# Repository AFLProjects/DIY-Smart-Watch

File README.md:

Project Overview
========

The project is an MCU based smartwatch. The MCU which is used is the [ATMEGA32U4](http://ww1.microchip.com/downloads/en/devicedoc/atmel-7766-8-bit-avr-atmega16u4-32u4_datasheet.pdf). The whole project is powered with the [3.7V 380mAh LQ-S1](https://i.ibb.co/z8Tqzwt/Capture.png) lithium battery.
I am also using an TFT 240 x 240 IPS [ST7789](https://www.rhydolabz.com/documents/33/ST7789.pdf) display with [SPI](https://fr.wikipedia.org/wiki/Serial_Peripheral_Interface). And the [RV-3028-C7](https://www.mouser.fr/datasheet/2/530/RV-3028-C7-1524919.pdf) Extreme Low Power RTC Module with [I2C](https://fr.wikipedia.org/wiki/I2C). In future revisions, an accelerometer will be added.

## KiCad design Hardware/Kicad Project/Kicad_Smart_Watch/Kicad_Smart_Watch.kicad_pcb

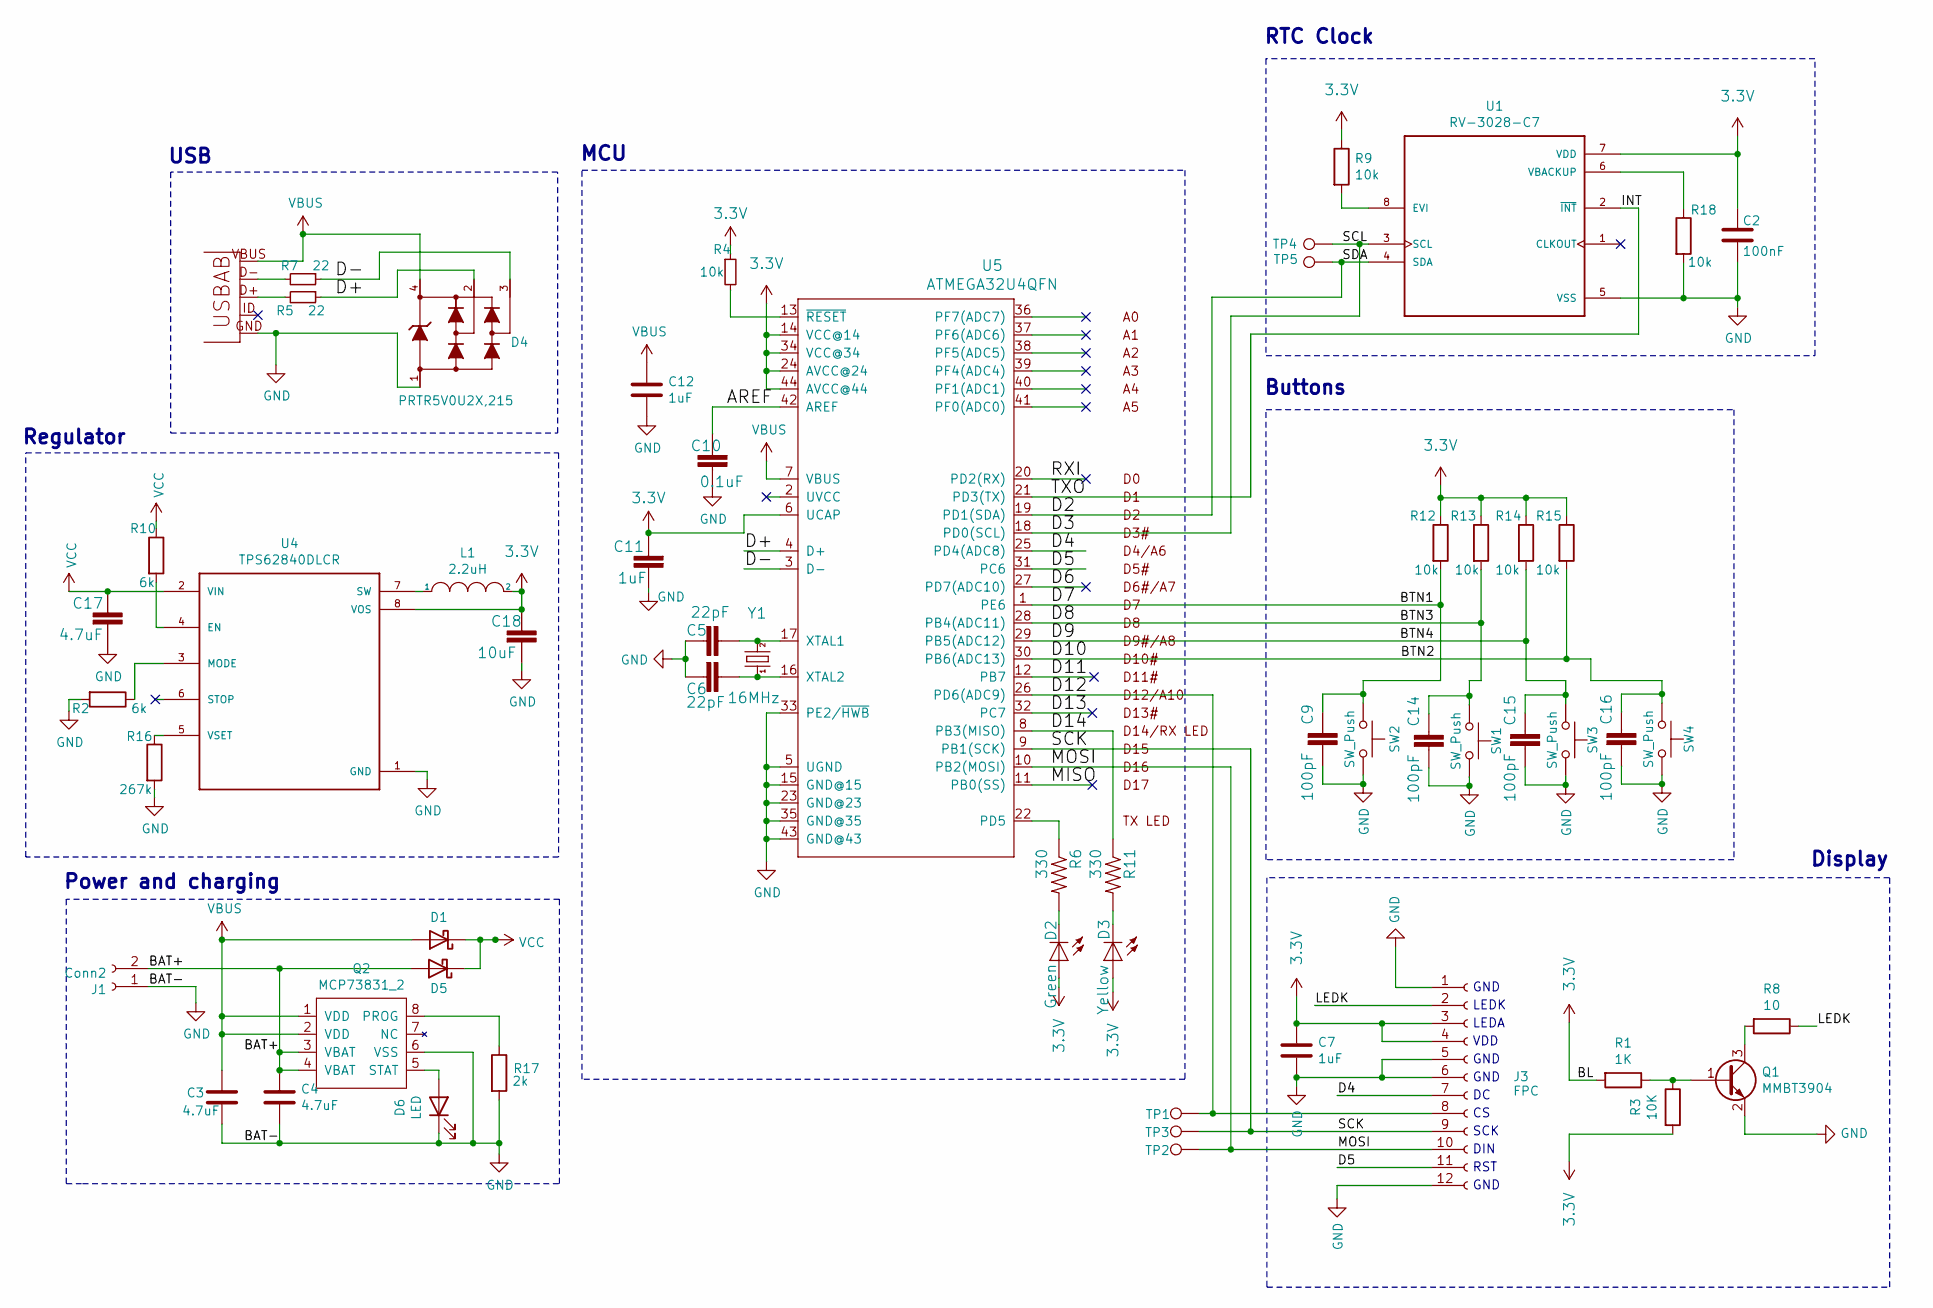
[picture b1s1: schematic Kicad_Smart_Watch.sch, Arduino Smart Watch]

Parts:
C2: 100nF; 0603
C3, C4, C17: 4.7uF; 0603
C5, C6: 22pF; 0603
C7, C11, C12: 1uF; 0603
C9, C14, C15, C16: 100pF; 0603
C10: 0.1uF; 0603
C18: 10uF; 0603
D1, D5: D_Schottky; 0603
D2: Green; D_0603_1608Metric
D3: Yellow; D_0603_1608Metric
D4: PRTR5V0U2X,215; SOT143B
D6: LED; 0603
J1: Conn2; 1X02
J3: FPC; bearlcd12pin
L1: 2.2uH; 0603
Q1: MMBT3904; SOT23-3
Q2: MCP73831_2; SON50P200X300X100-9N
R1: 1K; 0603
R2, R10: 6k; 0603
R3: 10K; 0603
R4, R9, R12, R13, R14, R15, R18: 10k; 0603
R5, R7: 22; 0603
R6, R11: 330; 0603
R8: 10; 0603
R16: 267k; 0603
R17: 2k; 0603
SW1, SW2, SW3, SW4: SW_Push; 1X02
TP1, TP2, TP3, TP4, TP5: TestPoint; TestPoint_Pad_1.0x1.0mm
U1: RV-3028-C7; IC_RV-3028-C7
U3: USB-AB; GCT_USB3155-XX-X_REVA
U4: TPS62840DLCR; SON50P200X150X100-8N
U5: ATMEGA32U4QFN; QFN50P700X700X100-45N
Y1: 16MHz; CRYSTAL-SMD-5X3.2-4PAD

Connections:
3.3V: C2.1, C7.1, C11.2, C18.1, D2.A, D3.A, J3.3, J3.4, L1.2, R1.2, R3.2, R4.1, R9.1, R12.1, R13.1, R14.1, R15.1, U1.7 (VDD), U4.8 (VOS), U5.6 (UCAP), U5.14 (VCC@14), U5.24 (AVCC@24), U5.34 (VCC@34), U5.44 (AVCC@44)
/AREF: C10.2, U5.42 (AREF)
/BAT+: C4.1, D5.2 (A), J1.2, Q2.3 (VBAT), Q2.4 (VBAT)
/BTN1: C9.1, R12.2, SW2.1, U5.1 (PE6)
/BTN2: C16.1, R15.2, SW4.1, U5.30 (PB6(ADC13))
/BTN3: C14.1, R13.2, SW1.1, U5.28 (PB4(ADC11))
/BTN4: C15.1, R14.2, SW3.1, U5.29 (PB5(ADC12))
/D2: TP5.1, U1.4 (SDA), U5.19 (PD1(SDA))
/D3: TP4.1, U1.3 (SCL), U5.18 (PD0(SCL))
/D4: J3.7, U5.25 (PD4(ADC8))
/D5: J3.11, U5.31 (PC6)
/D6: U5.27 (PD7(ADC10))
/D11: U5.12 (PB7)
/D12: J3.8, TP1.1, U5.26 (PD6(ADC9))
/D13: U5.32 (PC7)
/D14: R11.1, U5.8 (PB3(MISO))
/D+: D4.2, R7.1, U5.4 (D+)
/D-: D4.3, R5.1, U5.3 (D-)
/INT: U1.2 (~INT~), U5.21 (PD3(TX))
/LEDK: J3.2, R8.1
/MISO: U5.11 (PB0(SS))
/MOSI: J3.10, TP2.1, U5.10 (PB2(MOSI))
/RXI: U5.20 (PD2(RX))
/SCK: J3.9, TP3.1, U5.9 (PB1(SCK))
GND: C2.2, C3.2, C4.2, C5.2, C6.2, C7.2, C9.2, C10.1, C11.1, C12.2, C14.2, C15.2, C16.2, C17.2, C18.2, D4.1, D6.1 (K), J1.1, J3.1, J3.5, J3.6, J3.12, Q1.2 (E), Q2.6 (VSS), R2.2, R16.2, R17.2, R18.2, SW1.2, SW2.2, SW3.2, SW4.2, U1.5 (VSS), U3.GND, U4.1 (GND), U5.5 (UGND), U5.15 (GND@15), U5.23 (GND@23), U5.33 (PE2/~HWB), U5.35 (GND@35), U5.43 (GND@43); also elsewhere on the board
unnamed: C5.1, U5.17 (XTAL1), Y1.3 (2)
unnamed: C6.1, U5.16 (XTAL2), Y1.1
unnamed: D2.C, R6.2
unnamed: D3.C, R11.2
unnamed: D6.2 (A), Q2.5 (STAT)
unnamed: L1.1, U4.7 (SW)
unnamed: Q1.1 (B), R1.1, R3.1
unnamed: Q1.3 (C), R8.2
unnamed: Q2.8 (PROG), R17.1
unnamed: R2.1, U4.3 (MODE)
unnamed: R4.2, U5.13 (~RESET)
unnamed: R5.2, U3.D-
unnamed: R6.1, U5.22 (PD5)
unnamed: R7.2, U3.D+
unnamed: R9.2, U1.8 (EVI)
unnamed: R10.2, U4.4 (EN)
unnamed: R16.1, U4.5 (VSET)
unnamed: R18.1, U1.6 (VBACKUP)
VBUS: C3.1, C12.1, D1.2 (A), D4.4, Q2.1 (VDD), Q2.2 (VDD), U3.VBUS, U5.7 (VBUS)
VCC: C17.1, D1.1 (K), D5.1 (K), R10.1, U4.2 (VIN); also elsewhere on the board

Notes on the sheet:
USB
RTC Clock
Display
LEDK
LEDA
VDD
GND
SCK
DIN
RST
Buttons
MCU
Regulator
Power and charging

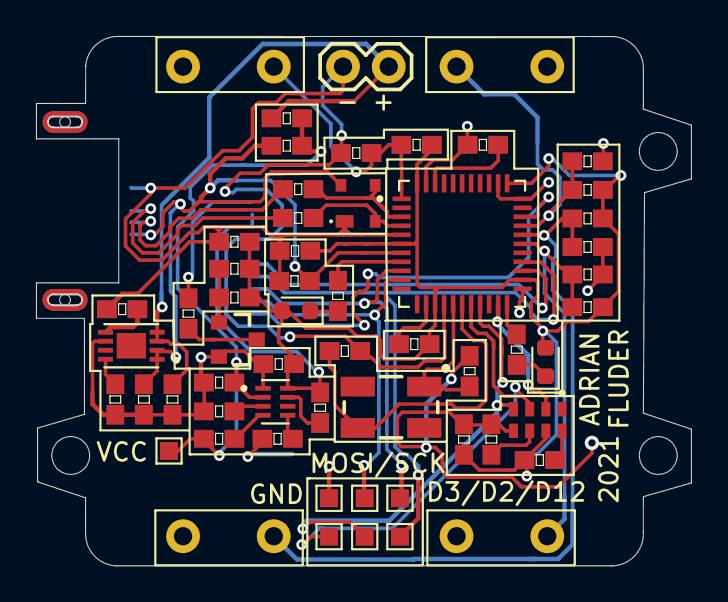
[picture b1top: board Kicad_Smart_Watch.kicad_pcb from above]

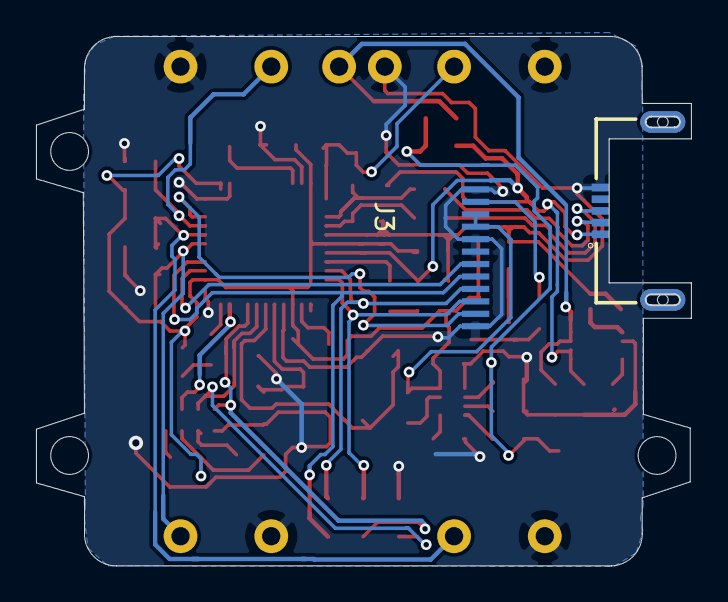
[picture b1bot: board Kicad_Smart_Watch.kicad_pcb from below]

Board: 2 copper layers, 36.3 x 29.4 mm, 60 parts (2 on the bottom side), 40 nets.

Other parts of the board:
GND: TestPoint; TestPoint_Pad_1.0x1.0mm
VCC: TestPoint; TestPoint_Pad_1.0x1.0mm

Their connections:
GND: GND.1; also elsewhere on the board
VCC: VCC.1; also elsewhere on the board

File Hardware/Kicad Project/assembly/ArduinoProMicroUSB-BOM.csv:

Designator,Quantity,Value,Footprint,LCSC Part #
"C3, C7, C11, C12, ",4,1uF,Capacitor_SMD:C_0402_1005Metric,C52923
"C4, C10, ",2,0.1uF,Capacitor_SMD:C_0402_1005Metric,C1525
"C5, C6, ",2,22pF,Capacitor_SMD:C_0402_1005Metric,C1555
"C8, C9, ",2,100nF,Capacitor_SMD:C_0402_1005Metric,C1525
"D1, ",1,DIODESOD,Diode_SMD:D_SOD-123,C8598
"D2, ",1,Green,Diode_SMD:D_0805_2012Metric,C2296
"D3, ",1,Yellow,Diode_SMD:D_0805_2012Metric,C2296
"D4, ",1,D,Diode_SMD:D_0805_2012Metric,C2296
"D5, ",1,LED,Diode_SMD:D_0805_2012Metric,C2296
"F1, ",1,500mA,Fuse:Fuse_1812_4532Metric,C151168
"LED1, ",1,Red,Diode_SMD:D_0805_2012Metric,C2296
"Q1, ",1,MMBT3904,Downloads:SOT23-3,C20526
"R1, R2, ",2,1K,Resistor_SMD:R_0603_1608Metric,C21190
"R3, ",1,10K,Resistor_SMD:R_0603_1608Metric,C25804
"R4, R12, R13, R14, R15, ",5,10k,Resistor_SMD:R_0603_1608Metric,C25804
"R5, R7, ",2,22,Resistor_SMD:R_0603_1608Metric,C23345
"R6, R10, R11, ",3,330,Resistor_SMD:R_0603_1608Metric,C23138
"R8, ",1,10,Resistor_SMD:R_0603_1608Metric,C22859
"R9, ",1,200,Resistor_SMD:R_0603_1608Metric,C8218
"RN1, RN2, ",2,R_Pack04,Resistor_SMD:R_Array_Concave_4x0603,C66697
"U1, ",1,DS3231M,Package_SO:SOIC-16W_7.5x10.3mm_P1.27mm,C37663
"U2, ",1,MIC5219,Downloads:SOT23-5,C145689
"U5, ",1,ATMEGA32U4QFN,Package_QFP:TQFP-44_10x10mm_P0.8mm,C44854
"Y1, ",1,16MHz,Downloads:CRYSTAL-SMD-5X3.2-4PAD,C16171

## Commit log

2020-10-25 first
2020-10-25 readme
2020-10-26 reademe
2020-10-26 readme file
2020-10-26 added reference schematics
2020-10-26 readmefile
2020-10-26 added schematic preview
2020-10-26 added image
2020-10-26 added img
2020-10-26 rev 0.1
2020-10-26 img added
2020-10-27 rev 0.2
2020-10-28 schematic checking
2020-10-28 readne
2020-10-28 rev 0,2
2020-10-28 rev 0.3
2020-10-28 img4
2020-10-28 img5
2020-10-29 updated schematic
2020-10-29 changelog
2020-10-29 schematic
2020-10-30 schematic pdf
2020-10-31 rev 0.4
2020-11-02 working on pcb
2020-11-04 finishing hardware design
2020-11-04 added new datasheet
2020-11-04 updated pcb img
2020-11-04 updated pcb
2020-11-06 checking schematic
2020-11-06 pcb checking
2020-11-07 checking pcb
2020-11-09 img2
2020-11-17 readme md
2020-11-17 3d print photos
2020-11-18 Added 3d models
2020-11-18 added 2d sketches
2020-11-18 rm & images
2020-11-18 updated 3d model
2020-11-18 3D model updated
2020-11-23 cleaned up folders
2020-11-23 updated project name
2020-12-06 updated mcu board pcb
2022-01-21 project continuation
2022-01-21 image update
2022-01-21 added images
2022-01-21 changing images
2022-01-21 updated images
2022-01-21 images updated
2022-01-21 images
